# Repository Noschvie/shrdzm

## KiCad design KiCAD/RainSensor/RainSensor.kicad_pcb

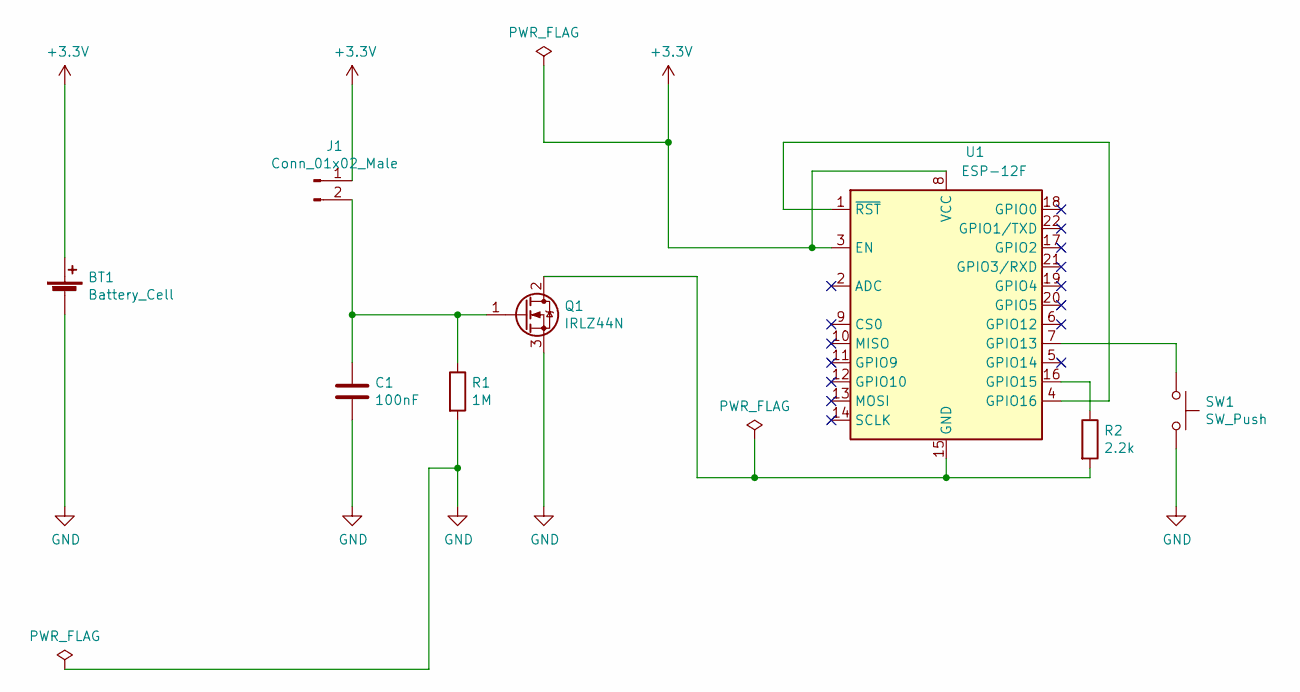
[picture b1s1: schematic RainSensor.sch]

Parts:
BT1: Battery_Cell; BatteryHolder_MPD_BH-18650-PC2
C1: 100nF; C_0805_2012Metric_Pad1.18x1.45mm_HandSolder
J1: Conn_01x02_Male; JST_PH_B2B-PH-K_1x02_P2.00mm_Vertical
Q1: IRLZ44N; TO-220-3_Horizontal_TabDown
R1: 1M; R_0805_2012Metric_Pad1.20x1.40mm_HandSolder
R2: 2.2k; R_0805_2012Metric_Pad1.20x1.40mm_HandSolder
SW1: SW_Push; SW_PUSH_6mm
U1: ESP-12F; ESP-12E

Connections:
+3V3: BT1.1 (+), J1.1, U1.3 (EN), U1.8 (VCC)
GND: BT1.2 (-), C1.2, Q1.3 (S), R1.2, SW1.2
unnamed: C1.1, J1.2, Q1.1 (G), R1.1
unnamed: Q1.2 (D), R2.2, U1.15 (GND)
unnamed: R2.1, U1.16 (GPIO15)
unnamed: SW1.1, U1.7 (GPIO13)
unnamed: U1.1 (~RST), U1.4 (GPIO16)

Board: 2 copper layers, 8 parts (1 on the bottom side), 7 nets, no tracks yet.
